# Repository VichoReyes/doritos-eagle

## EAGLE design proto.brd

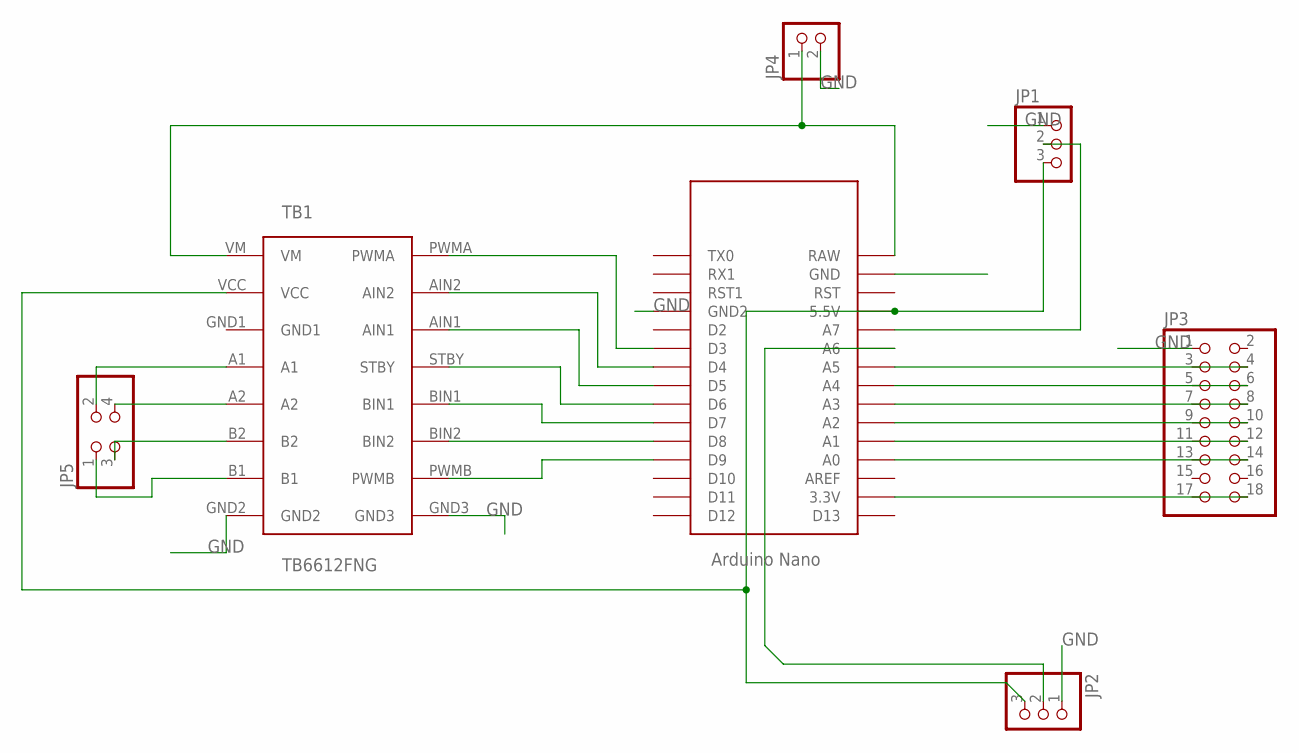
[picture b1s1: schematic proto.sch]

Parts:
JP1, JP2: PINHD-1X3; 1X03
JP3: PINHD-2X9; 2X09
JP4: PINHD-1X2; 1X02
JP5: PINHD-2X2; 2X02
TB1: TB6612FNG
U$1: NANO

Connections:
GND: JP1.1, JP2.1, JP3.1, JP4.2, TB1.GND2, TB1.GND3, U$1.GND, U$1.GND1 (GND2)
unnamed: TB1.PWMA, U$1.D3
unnamed: TB1.AIN2, U$1.D4
unnamed: TB1.AIN1, U$1.D5
unnamed: TB1.STBY, U$1.D6
unnamed: TB1.BIN1, U$1.D7
unnamed: TB1.BIN2, U$1.D8
unnamed: TB1.PWMB, U$1.D9
unnamed: JP5.2, TB1.A1
unnamed: JP4.1, TB1.VM, U$1.RAW
unnamed: JP3.4, U$1.A5
unnamed: JP5.4, TB1.A2
unnamed: JP5.3, TB1.B2
unnamed: JP5.1, TB1.B1
unnamed: JP3.6, U$1.A4
unnamed: JP3.8, U$1.A3
unnamed: JP3.10, U$1.A2
unnamed: JP1.2, U$1.A7
unnamed: JP3.12, U$1.A1
unnamed: JP3.14, U$1.A0
unnamed: JP3.18, U$1.3.3V
unnamed: JP2.2, U$1.A6
unnamed: JP1.3, JP2.3, TB1.VCC, U$1.5V (5.5V)

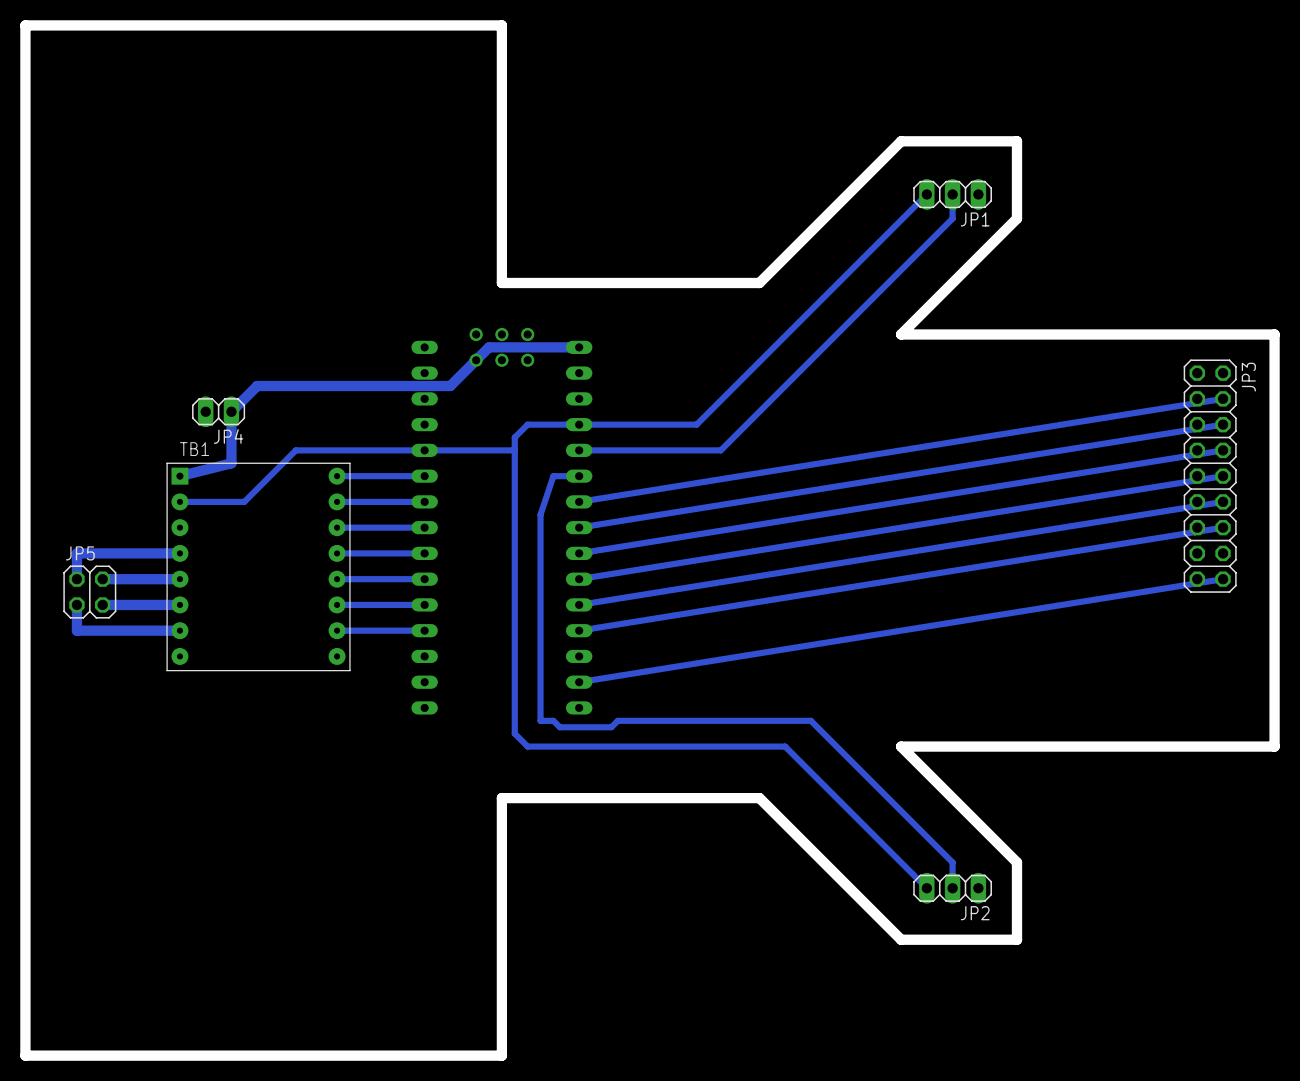
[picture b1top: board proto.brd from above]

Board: 2 copper layers, 123.2 x 101.6 mm, 7 parts (0 on the bottom side), 23 nets.

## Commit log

2018-10-12 arduino and H bridge connected
2018-10-12 schematic terminada, creo que decente
2018-10-13 finished schematic
    last one didn't use the correct pins
2018-10-16 eliminar tierras
2018-10-16 holi
2018-10-16 FINALMENTE
2018-10-16 holksadlkasdjf
2018-10-17 monton de weas
